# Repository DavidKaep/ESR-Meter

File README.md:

# ESR-Meter
A ESR Meter using only a TL074 Opamp

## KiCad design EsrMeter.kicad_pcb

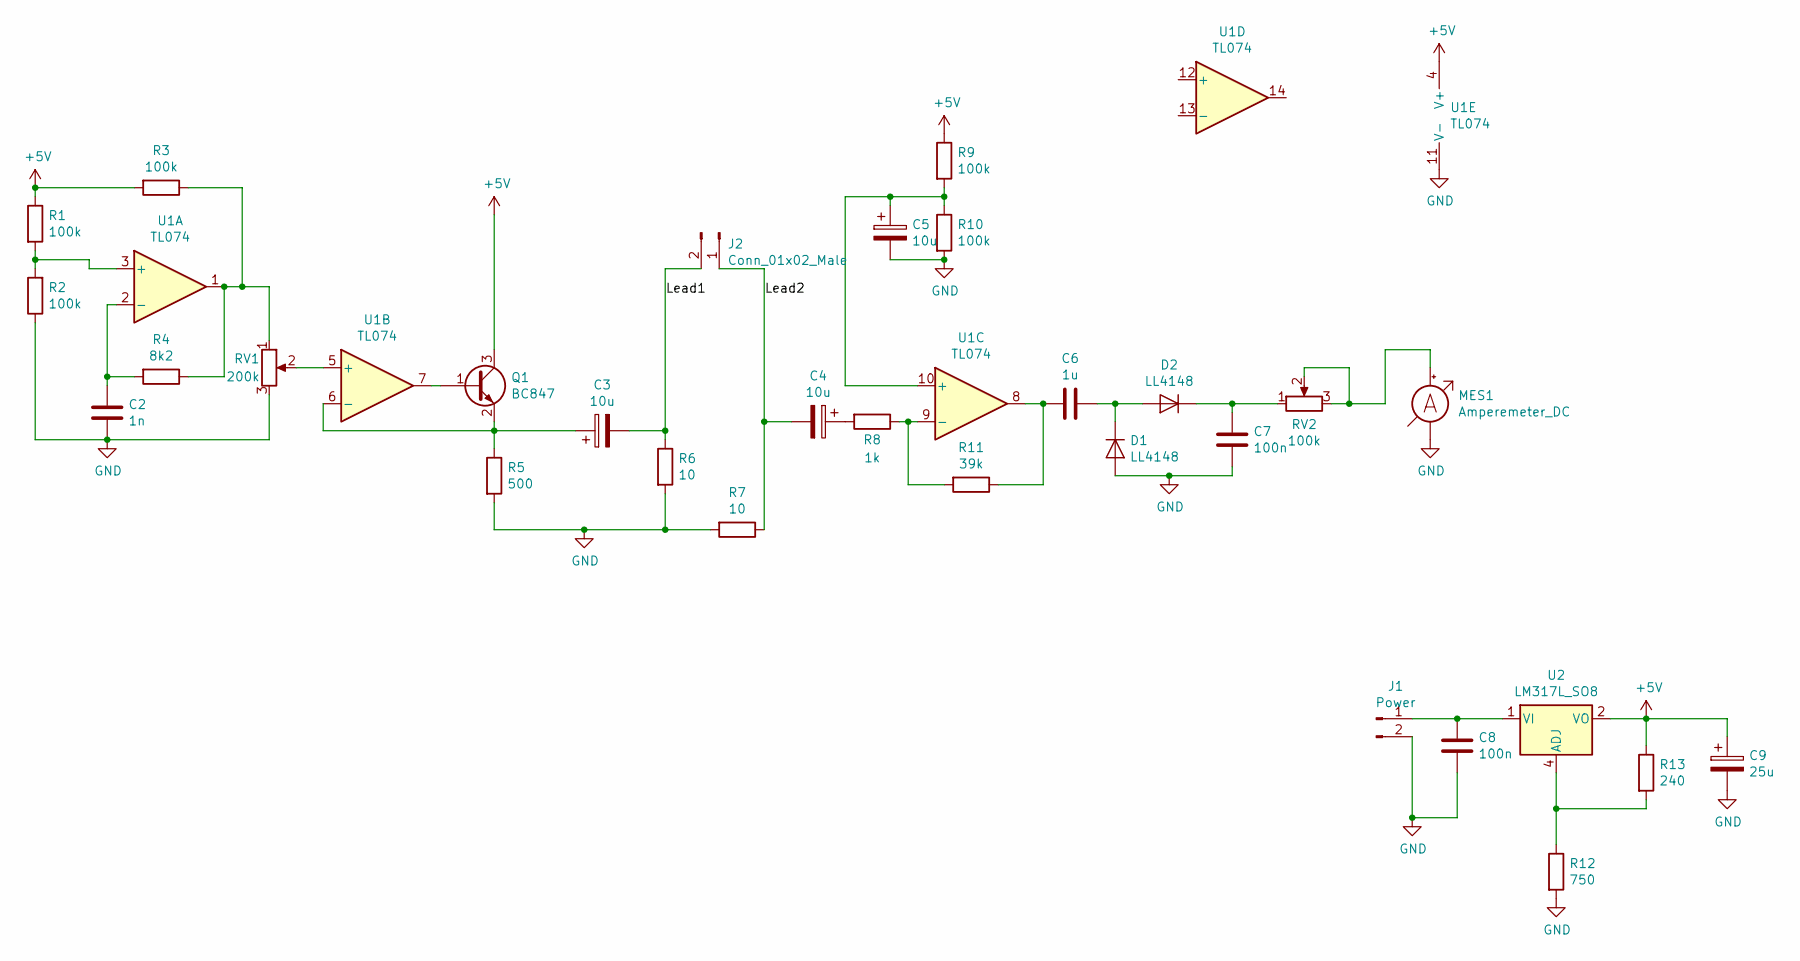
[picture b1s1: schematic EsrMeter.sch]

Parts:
C2: 1n; C_0805_2012Metric
C3, C4, C5: 10u; CP_Radial_D4.0mm_P2.00mm
C6: 1u; C_0805_2012Metric
C7, C8: 100n; C_0805_2012Metric
C9: 25u; CP_Radial_D4.0mm_P2.00mm
D1, D2: LL4148; D_MiniMELF
J1: Power; PinSocket_1x02_P2.54mm_Vertical
J2: Conn_01x02_Male; PinSocket_1x02_P2.54mm_Vertical
MES1: Amperemeter_DC; PinSocket_1x02_P2.54mm_Vertical
Q1: BC847; SOT-23
R1, R2, R3, R9, R10: 100k; R_0805_2012Metric
R4: 8k2; R_0805_2012Metric
R5: 500; R_0805_2012Metric
R6, R7: 10; R_0805_2012Metric
R8: 1k; R_0805_2012Metric
R11: 39k; R_0805_2012Metric
R12: 750; R_0805_2012Metric
R13: 240; R_0805_2012Metric
RV1: 200k; PinSocket_1x03_P2.54mm_Vertical
RV2: 100k; PinSocket_1x03_P2.54mm_Vertical
U1: TL074; SOIC-14_3.9x8.7mm_P1.27mm
U2: LM317L_SO8; SOIC-8_3.9x4.9mm_P1.27mm

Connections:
+5V: C9.1, Q1.3 (C), R1.1, R3.2, R9.1, R13.1, U1.4 (V+), U2.2 (VO), U2.3 (VO), U2.6 (VO), U2.7 (VO)
/Lead1: C3.2, J2.2, R6.1
/Lead2: C4.2, J2.1, R7.1
GND: C2.2, C5.2, C7.2, C8.2, C9.2, D1.2 (A), J1.2, MES1.1 (-), R2.1, R5.2, R6.2, R7.2, R10.2, R12.2, RV1.3, U1.11 (V-)
unnamed: C2.1, R4.2, U1.2 (-)
unnamed: C3.1, Q1.2 (E), R5.1, U1.6 (-)
unnamed: C4.1, R8.2
unnamed: C5.1, R9.2, R10.1, U1.10 (+)
unnamed: C6.1, D1.1 (K), D2.2 (A)
unnamed: C6.2, R11.1, U1.8
unnamed: C7.1, D2.1 (K), RV2.1
unnamed: C8.1, J1.1, U2.1 (VI)
unnamed: MES1.2 (+), RV2.2, RV2.3
unnamed: Q1.1 (B), U1.7
unnamed: R1.2, R2.2, U1.3 (+)
unnamed: R3.1, R4.1, RV1.1, U1.1
unnamed: R8.1, R11.2, U1.9 (-)
unnamed: R12.1, R13.2, U2.4 (ADJ)
unnamed: RV1.2, U1.5 (+)

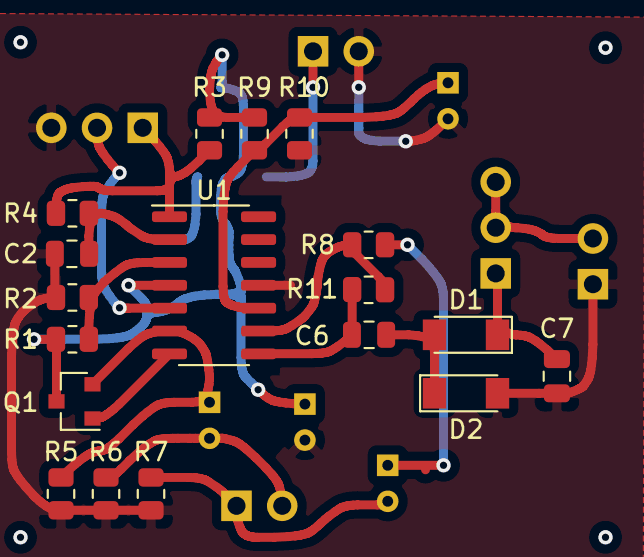
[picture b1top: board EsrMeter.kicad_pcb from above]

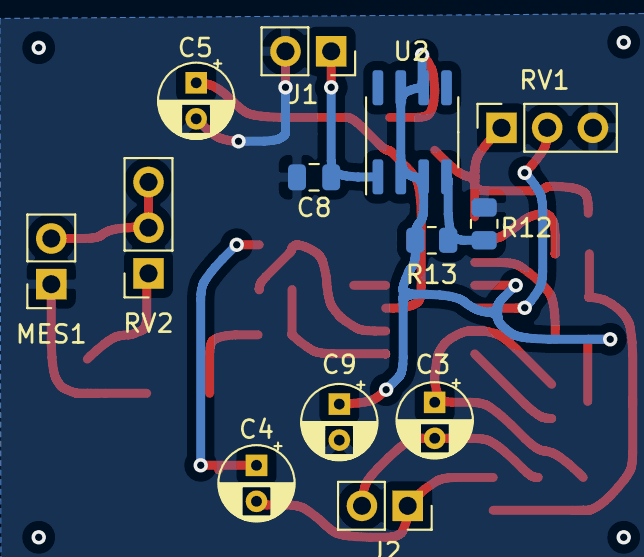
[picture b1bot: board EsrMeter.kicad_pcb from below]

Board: 2 copper layers, 31 parts (13 on the bottom side), 19 nets.

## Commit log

2021-01-22 Initialize Repo
